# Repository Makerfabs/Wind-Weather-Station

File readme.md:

# Wind Weather Station

```c++
/*
Version:		V2.0
Author:			Vincent
Create Date:	2021/2/23
Note:
	2021/7/20: Add a weather station project.
	2021/5/5:Add Seeed UV Sensor example.
	
*/
```
[toc]

[DIY Wind Weather Station and Remote Monitor via MQTT](https://www.youtube.com/watch?v=OUKzvni5h78)

# Makerfabs

[Makerfabs home page](https://www.makerfabs.com/)

[Makerfabs Wiki](https://makerfabs.com/wiki/index.php?title=Main_Page)

# Wind Weather Station

## Intruduce

### Product Link: [Open Wind Station GPRS/ MQTT](https://www.makerfabs.com/open-wind-statation-gprs-mqtt.html)

### Wiki Link:[Wind_Weather_Station](https://www.makerfabs.com/wiki/index.php?title=Wind_Weather_Station)

Weather station based on Maduino A9G.With onboard DHT11 temperature and humidity sensor, BMP280 air pressure sensor and SSD1306LCD screen.It can be connected with anemometer and PM2.5 air quality sensor.

## Feature

- Micro controller ATSAMD21G18, 32-Bit ARM Cortex M0+
- PM2.5 monitoring with expanded PM2.5 sensor
- GPS for locating
- Grove connectors for customers’ expanded testing
- OLED display for real-time checking& debugging
- Onboard buzzer/ SD card slot
- High-power 1000 mAH battery for long-term usage
- Solar panel charging
- With Case(but not water-proof), could be re-made for water-proof with glues easily
- Arduino compatible/ Support MQTT

### Front:

### Back:

### Interface:

1. Interface of anemometer

|   Pin   |   Mark   |   Definition   |
| ---- | ---- | ---- |
|   A   |   VCC   |   Power supply   |
|   B   |   GND   |   Grounding   |
|   C   |   A0   |    Data input  |

2. Interface of CO2 sensor

| Pin| 	Mark	|Definition                |
| ---- | ---- | ---- |
|   1   |   5V   |   Power supply   |
|   2   |   AD1   |  Data input    |
|   3   |   GND   |  Grounding    |
|   4   |   D10   |  LED Driving    |
|   5   |   GND   |  LED grounding    |
|   6   |   VLED   | LED Power supply     |

3. Other interfaces

| Pin| 	Mark	|Definition                |
| ---- | ---- | ---- |
|   a   |      | GND |
|   b   |      | VCC |
| c |      | A5 |
| d |      | A4 |
| e |      | GND |
| f | | VCC |
| g |      | SDA |
| h |      | SCL |

# Example

## Compiler Options

Choice Arduino Zero (Native USB Port).

## weather_show_default

Factory default program, collect temperature, humidity, air pressure, wind speed, PM2.5 index, the sensor data display on SSD1306.

- Connect anemometer or air quality sensor (or both) to weather station.
- Connect to battery or USB cable.
- LCD screen will show sensor value.

## at_demo

A simple AT directive demo is provided.

## weather_MQTT

A simple example of MQTT communication. Data is sent by MQTT protocol through A9G module. Need a SIM card that can be connected to the Internet.

## low_power

A simple low-power test program that turns off power to the A9G and all sensors and puts the SAMD21 to sleep.

# Project : Weather Station

**A long-maintained weather station project, real-time weather from Makerfabs can be accessed via ThingSpeak and Makerfabs Wiki (Shenzhen, China).**

The weather link is as follows:

[Makerfabs Wiki Weather](https://www.makerfabs.com/wiki/index.php?title=Weather_Show)

[ThingSpeak Show](https://thingspeak.com/channels/1243124)

[HackDay.io wind weather station](https://hackaday.io/project/177972-wind-weather-station)

## Code

The code is divided into two parts, one is the Weather Station, which measures the weather data and sends it to ThingSpeak and MQTT servers.

And there is a use of ESP32 as a terminal to receive real-time information code.

## Weather Analysis

The test lasted for ten days in June, and the analysis data are as follows.

And I also make a python file to analyse data, like max or min temperature.

Code is in : \Wind-Weather-Station\Project_WeatherStation\csv_read\csv_test.py

## 3D file

Weather station box and anemometer, wind direction gauge, fixed structure of solar panel.

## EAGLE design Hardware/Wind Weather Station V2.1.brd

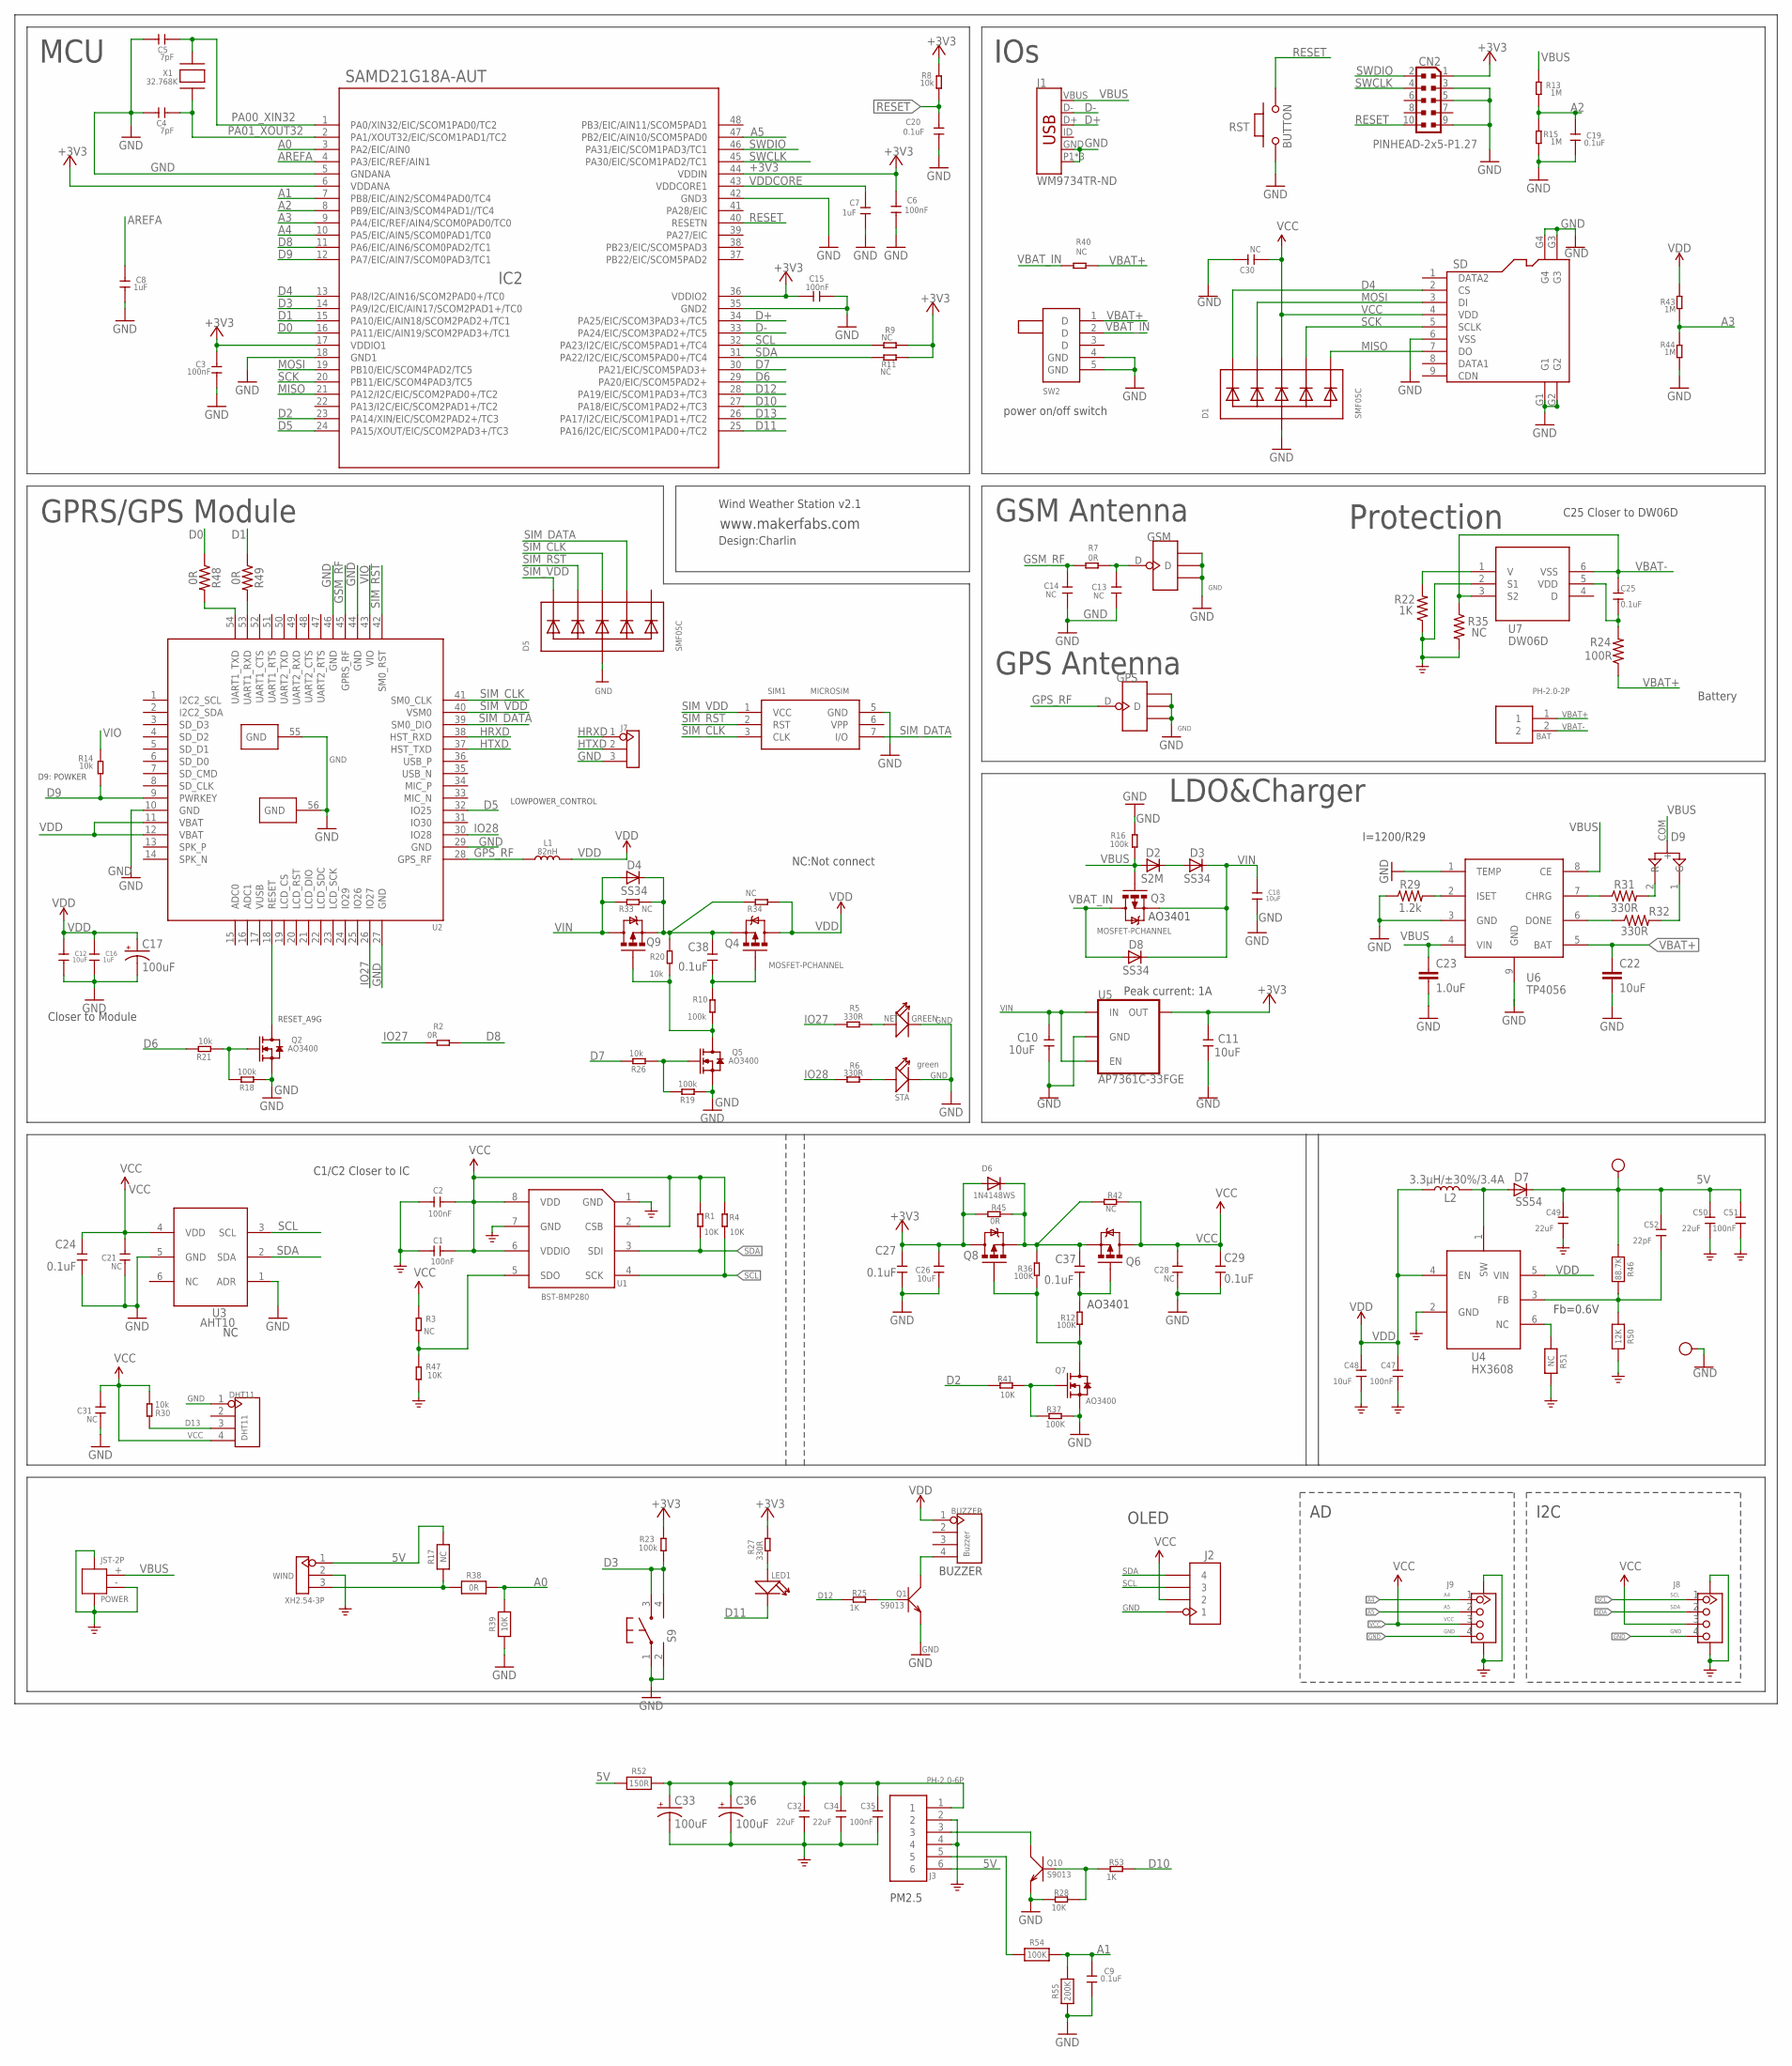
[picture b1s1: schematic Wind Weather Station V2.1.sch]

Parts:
5V: TEST-POINT'4545'; TP-D45MIL
BAT: PH-2.0-2P
BUZZER: Buzzer; 4P-65/35ROUND
C1, C2, C35, C47, C51: 100nF; C0603
C3, C6, C15: 100nF; 0603
C4, C5: 7pF; 0603
C7, C8, C16: 1uF; 0603
C9, C19, C20, C24, C25, C27, C29, C37, C38: 0.1uF; 0603
C10, C11, C12, C18, C26: 10uF; 0603
C13, C14: NC; 0402
C17, C33, C36: 100uF; EIA3528
C21, C28, C31: NC; 0603
C22: 10uF; 1206
C23: 1.0uF; 0603
C30: NC; DISCRETE_C0603
C32, C34, C49, C50: 22uF; C0603
C48: 10uF; C0603
C52: 22pF; C0603
CN2: PINHEAD-2x5-P1.27; PINHEAD_2X05_127
D1, D5: SMF05C; SOT363
D2: S2M; DO-214AC
D3, D4, D8: SS34; DO-214AC
D6: 1N4148WS; SOD-323F
D7: SS54; DO-214AC
D9: LED-ARG-3P'-3MM'; LED-3P-2.54-3MM
DHT11: DHT11; 4P-65/35ROUND
GND: TEST-POINT'4545'; TP-D45MIL
GPS: ANTENNA-U-FL; 4P-U-FL
GSM: ANTENNA-U-FL; 4P-U-FL
IC2: SAMD21G18A-AUT; TQFP48-7X7
J1: WM9734TR-ND; USB-B-MICRO-SMD_VERT
J2: HEADER-1X4P; SMD4-2.54P
J3: PH-2.0-6P
J7: HEADER-3P-2.54; 3P-2.54
J8, J9: GROVE-CONNECTOR-SMD'90D'; HW4-SMD-2.0-90D
L1: 82nH; L0603
L2: 3.3µH/±30%/3.4A; CR54
LED1: DISCRETE_LED0603; DISCRETE_LED-0603
NET: GREEN; DISCRETE_LED-0603
POWER: JST-2P; HW2-SMD-2.0-90D
Q1, Q10: S9013; SOT23
Q2, Q5: AO3400; SOT23@1
Q3, Q4, Q6, Q8, Q9: MOSFET-PCHANNEL; SOT23-3
Q7: AO3400; DISCRETE_SOT23
R1, R4, R28, R41, R47: 10K; R0603
R2, R7, R45: 0R; R0603
R3, R9, R11, R33, R34, R40, R42: NC; R0603
R5, R6, R27: 330R; R0603
R8, R14, R20, R21, R26, R30: 10k; R0603
R10, R16, R18, R19, R23: 100k; R0603
R12, R36, R37: 100K; R0603
R13, R15, R43, R44: 1M; R0603
R17, R51: NC; 0603-NO
R22: 1K; 0603
R24: 100R; 0603
R25, R53: 1K; R0603
R29: 1.2k; 0603
R31, R32: 330R; 0603
R35: NC; 0603
R38: 0R; 0603-NO
R39: 10K; 0603-NO
R46: 88.7K; 0603-NO
R48, R49: 0R; 0603
R50: 12K; 0603-NO
R52: 150R; 0603-NO
R54: 100K; 0603-NO
R55: 200K; 0603-NO
RST: BUTTON; 157SW
S9: SWITCHES; SMD4-6*6
SD: HOLDER-MICROSD-9P; 9P-SMD-W/-RING
SIM1: MICROSIM
STA: green; LED-0603
SW2: SWITCH; DIP5-8.6*4.5MM
U1: BST-BMP280; LGA8-0.65-2X2.5X0.95MM
U2: A9G
U3: AHT10; SMD6-127P-400L500W
U4: HX3608; SOT-23-6
U5: AP7361C-33FGE; 8-UDFN
U6: TP4056; SOP8-1.27P
U7: DW06D; SOT-23-6
WIND: XH2.54-3P
X1: 32.768K; XTAL3215

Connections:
5V: 5V.T, C49.1, C50.1, C51.1, C52.1, D7.C, J3.6, R17.2, R46.1, R52.1, WIND.1
+3V3: C3.2, C6.1, C11.2, C15.1, C26.2, C27.2, CN2.1, D6.A, IC2.6 (VDDANA), IC2.17 (VDDIO1), IC2.36 (VDDIO2), IC2.44 (VDDIN), Q8.3 (D), R8.2, R9.2, R11.2, R23.2, R27.2, R45.2, U5.1 (OUT)
A0: IC2.3 (PA2/EIC/AIN0), R38.2, R39.2
A1: C9.1, IC2.7 (PB8/EIC/AIN2/SCOM4PAD0/TC4), R54.2, R55.2
A2: C19.1, IC2.8 (PB9/EIC/AIN3/SCOM4PAD1//TC4), R13.1, R15.2
A3: IC2.9 (PA4/EIC/REF/AIN4/SCOM0PAD0/TC0), R43.1, R44.2
A4: IC2.10 (PA5/EIC/AIN5/SCOM0PAD1/TC0), J9.1
A5: IC2.47 (PB2/EIC/AIN10/SCOM5PAD0), J9.2
AREFA: C8.1, IC2.4 (PA3/EIC/REF/AIN1)
D0: IC2.16 (PA11/EIC/AIN19/SCOM2PAD3+/TC1), R48.1
D1: IC2.15 (PA10/EIC/AIN18/SCOM2PAD2+/TC1), R49.1
D2: IC2.23 (PA14/XIN/EIC/SCOM2PAD2+/TC3), R41.2
D3: IC2.14 (PA9/I2C/EIC/AIN17/SCOM2PAD1+/TC0), R23.1, S9.3, S9.4
D4: D1.1 (C1), IC2.13 (PA8/I2C/AIN16/SCOM2PAD0+/TC0), SD.2 (CS)
D5: IC2.24 (PA15/XOUT/EIC/SCOM2PAD3+/TC3), U2.32 (IO25)
D6: IC2.29 (PA20/EIC/SCOM5PAD2+), R21.2
D7: IC2.30 (PA21/EIC/SCOM5PAD3+), R26.2
D8: IC2.11 (PA6/EIC/AIN6/SCOM0PAD2/TC1), R2.2
D9: IC2.12 (PA7/EIC/AIN7/SCOM0PAD3/TC1), R14.1, U2.9 (PWRKEY)
D10: IC2.27 (PA18/EIC/SCOM1PAD2+/TC3), R53.2
D11: IC2.25 (PA16/I2C/EIC/SCOM1PAD0+/TC2), LED1.-
D12: IC2.28 (PA19/EIC/SCOM1PAD3+/TC3), R25.1
D13: DHT11.3, IC2.26 (PA17/I2C/EIC/SCOM1PAD1+/TC2), R30.1
D+: IC2.34 (PA25/EIC/SCOM3PAD3+/TC5), J1.D+
D-: IC2.33 (PA24/EIC/SCOM3PAD2+/TC5), J1.D-
DONE: R32.1, U6.6 (DONE)
GND: C1.2, C2.2, C3.1, C4.2, C5.2, C6.2, C7.2, C8.2, C9.2, C10.1, C11.1, C12.1, C13.1, C14.1, C15.2, C16.1, C17.C (-), C18.1, C19.2, C20.1, C21.1, C22.2, C23.2, C24.1, C26.1, C27.1, C28.1, C29.1, C30.1, C31.1, C32.2, C33.C (-), C34.2, C35.2, C36.C (-), C47.2, C48.2, C49.2, C50.2, C51.2, CN2.3, CN2.5, CN2.9, D1.2 (A), D5.2 (A), DHT11.1, GND.T, GPS.GND1, GPS.GND2, GPS.GND3, GSM.GND1, GSM.GND2, GSM.GND3, IC2.5 (GNDANA), IC2.18 (GND1), IC2.35 (GND2), IC2.42 (GND3), J1.GND, J1.P1 (SHIELD), J1.P2 (SHIELD), J1.P3 (SHIELD), J2.1, J3.2, J3.4, J7.3, J8.4, J8.SS1, J8.SS2, J9.4, J9.SS1, J9.SS2, NET.-, POWER.3, POWER.4, POWER.- (2), Q1.2 (E), Q2.2 (S), Q5.2 (S), Q7.2 (S), Q10.2 (E), R15.1, R16.2, R18.1, R19.1, R22.1, R28.1, R29.1, R35.2, R37.1, R39.1, R44.1, R47.1, R50.2, R51.2, R55.1, RST.2, S9.1, S9.2, SD.6 (VSS), SD.G1, SD.G2, SD.G3, SD.G4, SIM1.5 (GND), STA.-, SW2.4 (GND), SW2.5 (GND), U1.1 (GND), U1.7 (GND), U2.10 (GND), U2.27 (GND), U2.29 (GND), U2.44 (GND), U2.46 (GND), U2.55 (GND), U2.56 (GND), U3.1 (ADR), U3.5 (GND), U4.2 (GND), U5.4 (GND), U5.EP (GND), U6.1 (TEMP), U6.3 (GND), U6.9 (GND), U7.2 (S1), WIND.2
GPS_RF: GPS.D, L1.1, U2.28 (GPS_RF)
GSM_RF: C14.2, R7.1, U2.45 (GPRS_RF)
HRXD: J7.1, U2.38 (HST_RXD)
HTXD: J7.2, U2.37 (HST_TXD)
IO27: R2.1, R5.1, U2.26 (IO27)
IO28: R6.1, U2.30 (IO28)
ISET: R29.2, U6.2 (ISET)
MISO: D1.6 (C5), IC2.21 (PA12/I2C/EIC/SCOM2PAD0+/TC2), SD.7 (DO)
MOSI: D1.3 (C2), IC2.19 (PB10/EIC/SCOM4PAD2/TC5), SD.3 (DI)
unnamed: R6.2, STA.+
unnamed: D2.C, D3.A
unnamed: C38.1, Q4.1 (G), R10.2
unnamed: Q5.1 (G), R19.2, R26.1
unnamed: LED1.+, R27.1
unnamed: C37.2, D6.C, Q6.2 (S), Q8.2 (S), R36.2, R42.2, R45.1
unnamed: NET.+, R5.2
unnamed: Q2.3 (D), U2.18 (RESET)
unnamed: BUZZER.4, Q1.3 (C)
unnamed: R17.1, R38.1, WIND.3
unnamed: C38.2, D4.C, Q4.2 (S), Q9.2 (S), R20.2, R33.1, R34.2
unnamed: Q2.1 (G), R18.2, R21.1
unnamed: D9.1 (G), R32.2
unnamed: R31.1, U6.7 (CHRG)
unnamed: Q7.3 (D), Q8.1 (G), R12.1, R36.1
unnamed: C25.2, R24.2, U7.5 (VDD)
unnamed: R22.2, U7.1 (V)
unnamed: D9.2 (R), R31.2
unnamed: Q7.1 (G), R37.2, R41.1
unnamed: R3.1, R47.2, U1.5 (SDO)
unnamed: R49.2, U2.53 (UART1_RXD)
unnamed: R48.2, U2.54 (UART1_TXD)
unnamed: D7.A, L2.P$2 (2), U4.1 (SW)
unnamed: Q1.1 (B), R25.2
unnamed: C52.2, R46.2, R50.1, U4.3 (FB)
unnamed: R51.1, U4.6 (NC)
unnamed: C32.1, C33.A (+), C34.1, C35.1, C36.A (+), J3.1, R52.2
unnamed: Q10.1 (B), R28.2, R53.1
unnamed: J3.3, Q10.3 (C)
unnamed: J3.5, R54.1
unnamed: Q5.3 (D), Q9.1 (G), R10.1, R20.1
unnamed: C37.1, Q6.1 (G), R12.2
unnamed: C13.2, GSM.D, R7.2
PA00_XIN32: C5.1, IC2.1 (PA0/XIN32/EIC/SCOM1PAD0/TC2), X1.P$2
PA01_XOUT32: C4.1, IC2.2 (PA1/XOUT32/EIC/SCOM1PAD1/TC2), X1.P$1
RESET: C20.2, CN2.10, IC2.40 (RESETN), R8.1, RST.1
SCK: D1.5 (C4), IC2.20 (PB11/EIC/SCOM4PAD3/TC5), SD.5 (SCLK)
SCL: IC2.32 (PA23/I2C/EIC/SCOM5PAD1+/TC4), J2.3, J8.1, R4.1, R9.1, U1.4 (SCK), U3.3 (SCL)
SDA: IC2.31 (PA22/I2C/EIC/SCOM5PAD0+/TC4), J2.4, J8.2, R1.1, R11.1, U1.3 (SDI), U3.2 (SDA)
SIM_CLK: D5.4 (C3), SIM1.3 (CLK), U2.41 (SM0_CLK)
SIM_DATA: D5.5 (C4), SIM1.7 (I/O), U2.39 (SM0_DIO)
SIM_RST: D5.3 (C2), SIM1.2 (RST), U2.42 (SM0_RST)
SIM_VDD: D5.1 (C1), SIM1.1 (VCC), U2.40 (VSM0)
SWCLK: CN2.4, IC2.45 (PA30/EIC/SCOM1PAD2/TC1)
SWDIO: CN2.2, IC2.46 (PA31/EIC/SCOM1PAD3/TC1)
VBAT+: BAT.1, C22.1, R24.1, R40.2, SW2.1 (D), U6.5 (BAT)
VBAT-: BAT.2, C25.1, R35.1, U7.3 (S2), U7.6 (VSS)
VBAT_IN: D8.A, Q3.3 (D), R40.1, SW2.2 (D)
VBUS: C23.1, D2.A, D9.COM (+), J1.VBUS, POWER.+ (1), Q3.1 (G), R13.2, R16.1, U6.4 (VIN), U6.8 (CE)
VCC: C1.1, C2.1, C21.2, C24.2, C28.2, C29.2, C30.2, C31.2, D1.4 (C3), DHT11.4, J2.2, J8.3, J9.3, Q6.3 (D), R1.2, R3.2, R4.2, R30.2, R42.1, SD.4 (VDD), U1.2 (CSB), U1.6 (VDDIO), U1.8 (VDD), U3.4 (VDD)
VDD: BUZZER.1, C12.2, C16.2, C17.A (+), C47.1, C48.1, L1.2, L2.P$1 (1), Q4.3 (D), R34.1, R43.2, U2.11 (VBAT), U2.12 (VBAT), U4.4 (EN), U4.5 (VIN)
VDDCORE: C7.1, IC2.43 (VDDCORE1)
VIN: C10.2, C18.2, D3.C, D4.A, D8.C, Q3.2 (S), Q9.3 (D), R33.2, U5.5 (EN), U5.8 (IN)
VIO: R14.2, U2.43 (VIO)

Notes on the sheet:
BUZZER
GSM Antenna
GPRS/GPS Module
LOWPOWER_CONTROL
RESET_A9G
D9: POWKER
Peak current: 1A
www.makerfabs.com
MCU
IOs
LDO&Charger
GPS Antenna
Design:Charlin
Closer to Module
AO3401
I=1200/R29
Wind Weather Station v2.1
NC:Not connect
Battery
C25 Closer to DW06D
Protection
I2C
C1/C2 Closer to IC
power on/off switch
OLED
Fb=0.6V
PM2.5

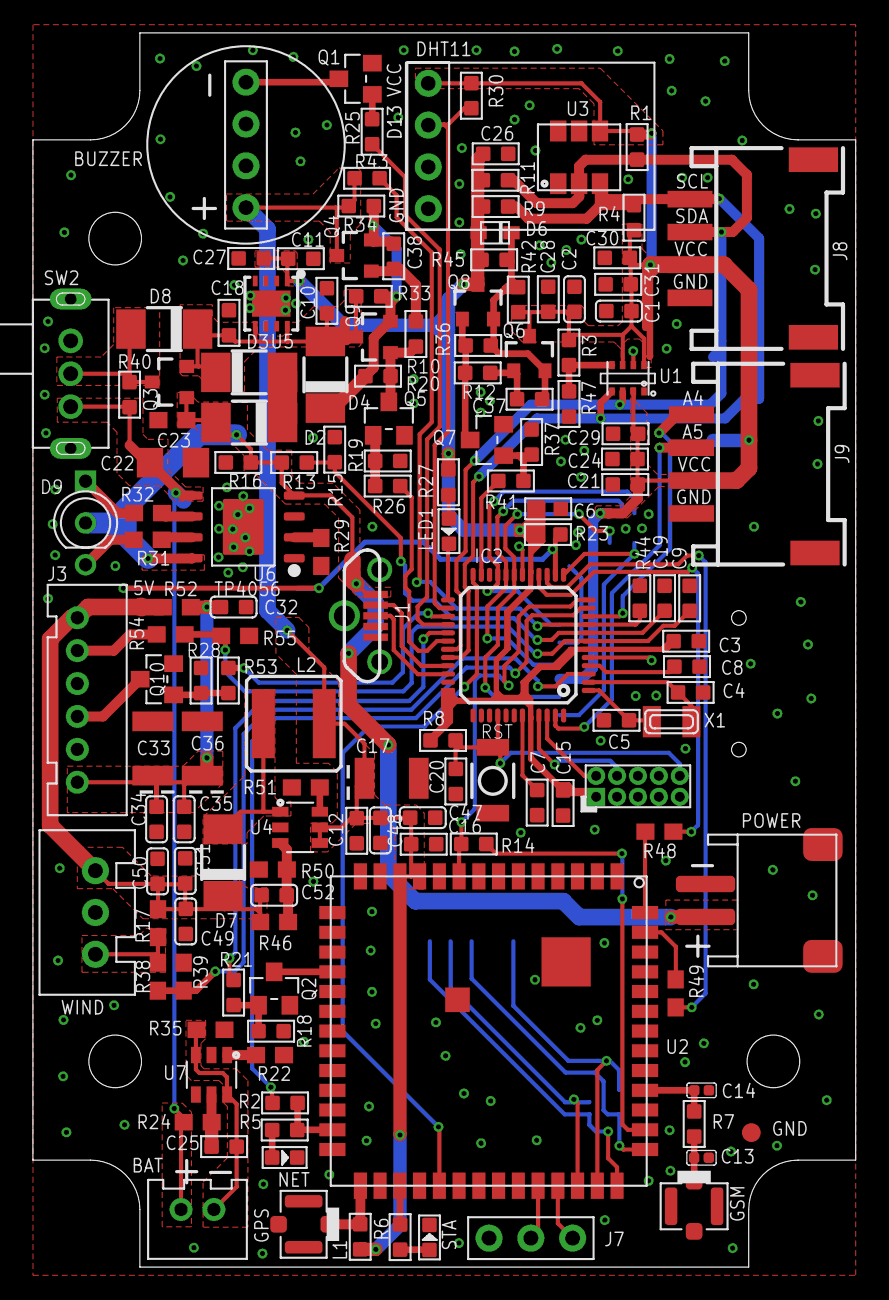
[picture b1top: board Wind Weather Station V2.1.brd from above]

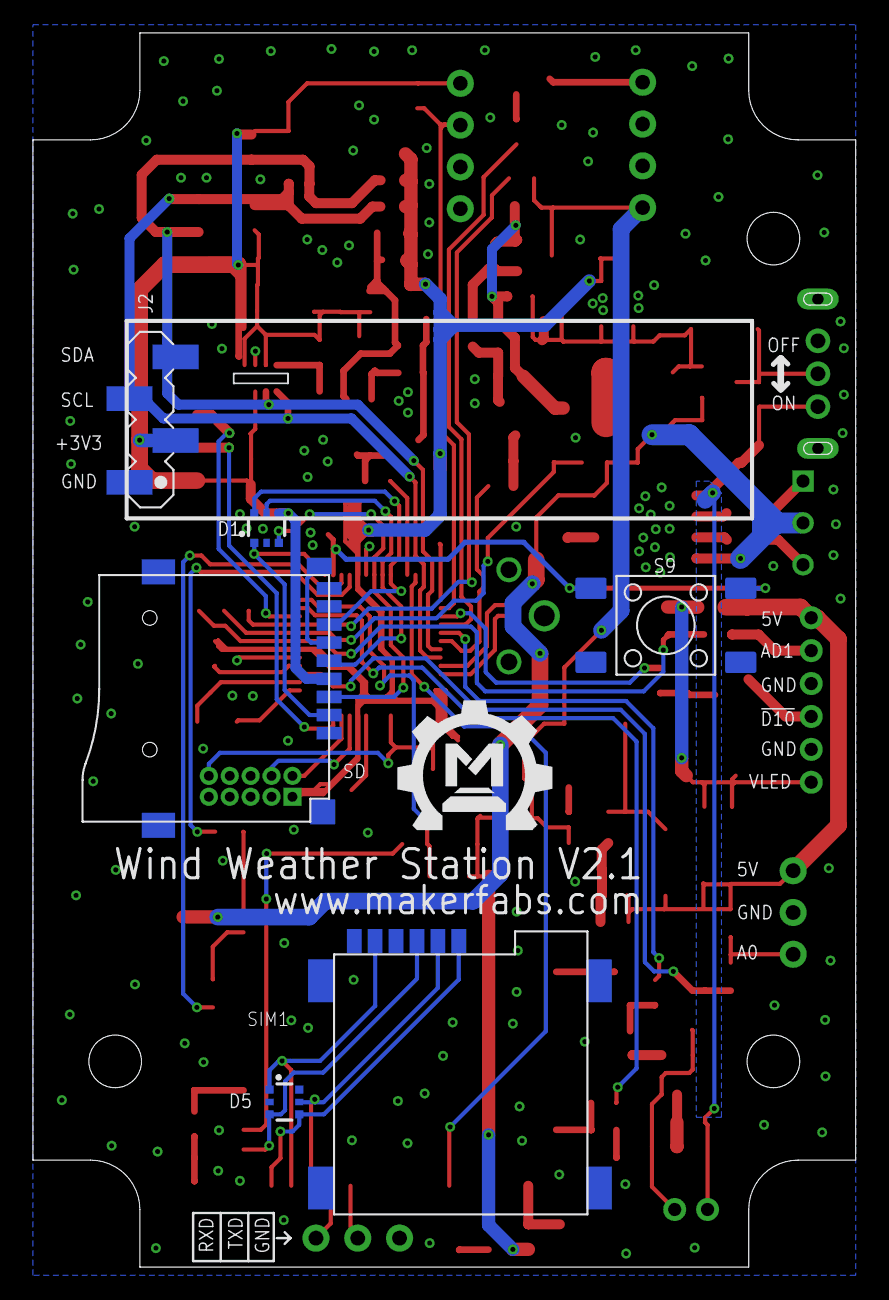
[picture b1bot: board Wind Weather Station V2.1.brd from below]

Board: 2 copper layers, 50.0 x 75.0 mm, 154 parts (7 on the bottom side), 90 nets.

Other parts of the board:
U$2: MAKERFABS-0.3

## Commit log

2021-02-23 Create project
2021-02-27 Add at demo
2021-03-13 Add low power example
2021-03-23 Fix bug
2021-04-15 Create
2021-04-16 fix bug
2021-04-22 add the unit
2021-04-28 add hardware
2021-05-05 Add Seeed UV sensor support
2021-05-05 Add product picture
2021-05-07 Create app
2021-07-20 Add weather project

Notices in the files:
parts and their libraries:
microbuilder: This work is placed in the public domain, and may be freely used for commercial and non-commercial work with the following conditions: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
SparkFun-Capacitors: Licensing: Creative Commons ShareAlike 4.0 International - https://creativecommons.org/licenses/by-sa/4.0
